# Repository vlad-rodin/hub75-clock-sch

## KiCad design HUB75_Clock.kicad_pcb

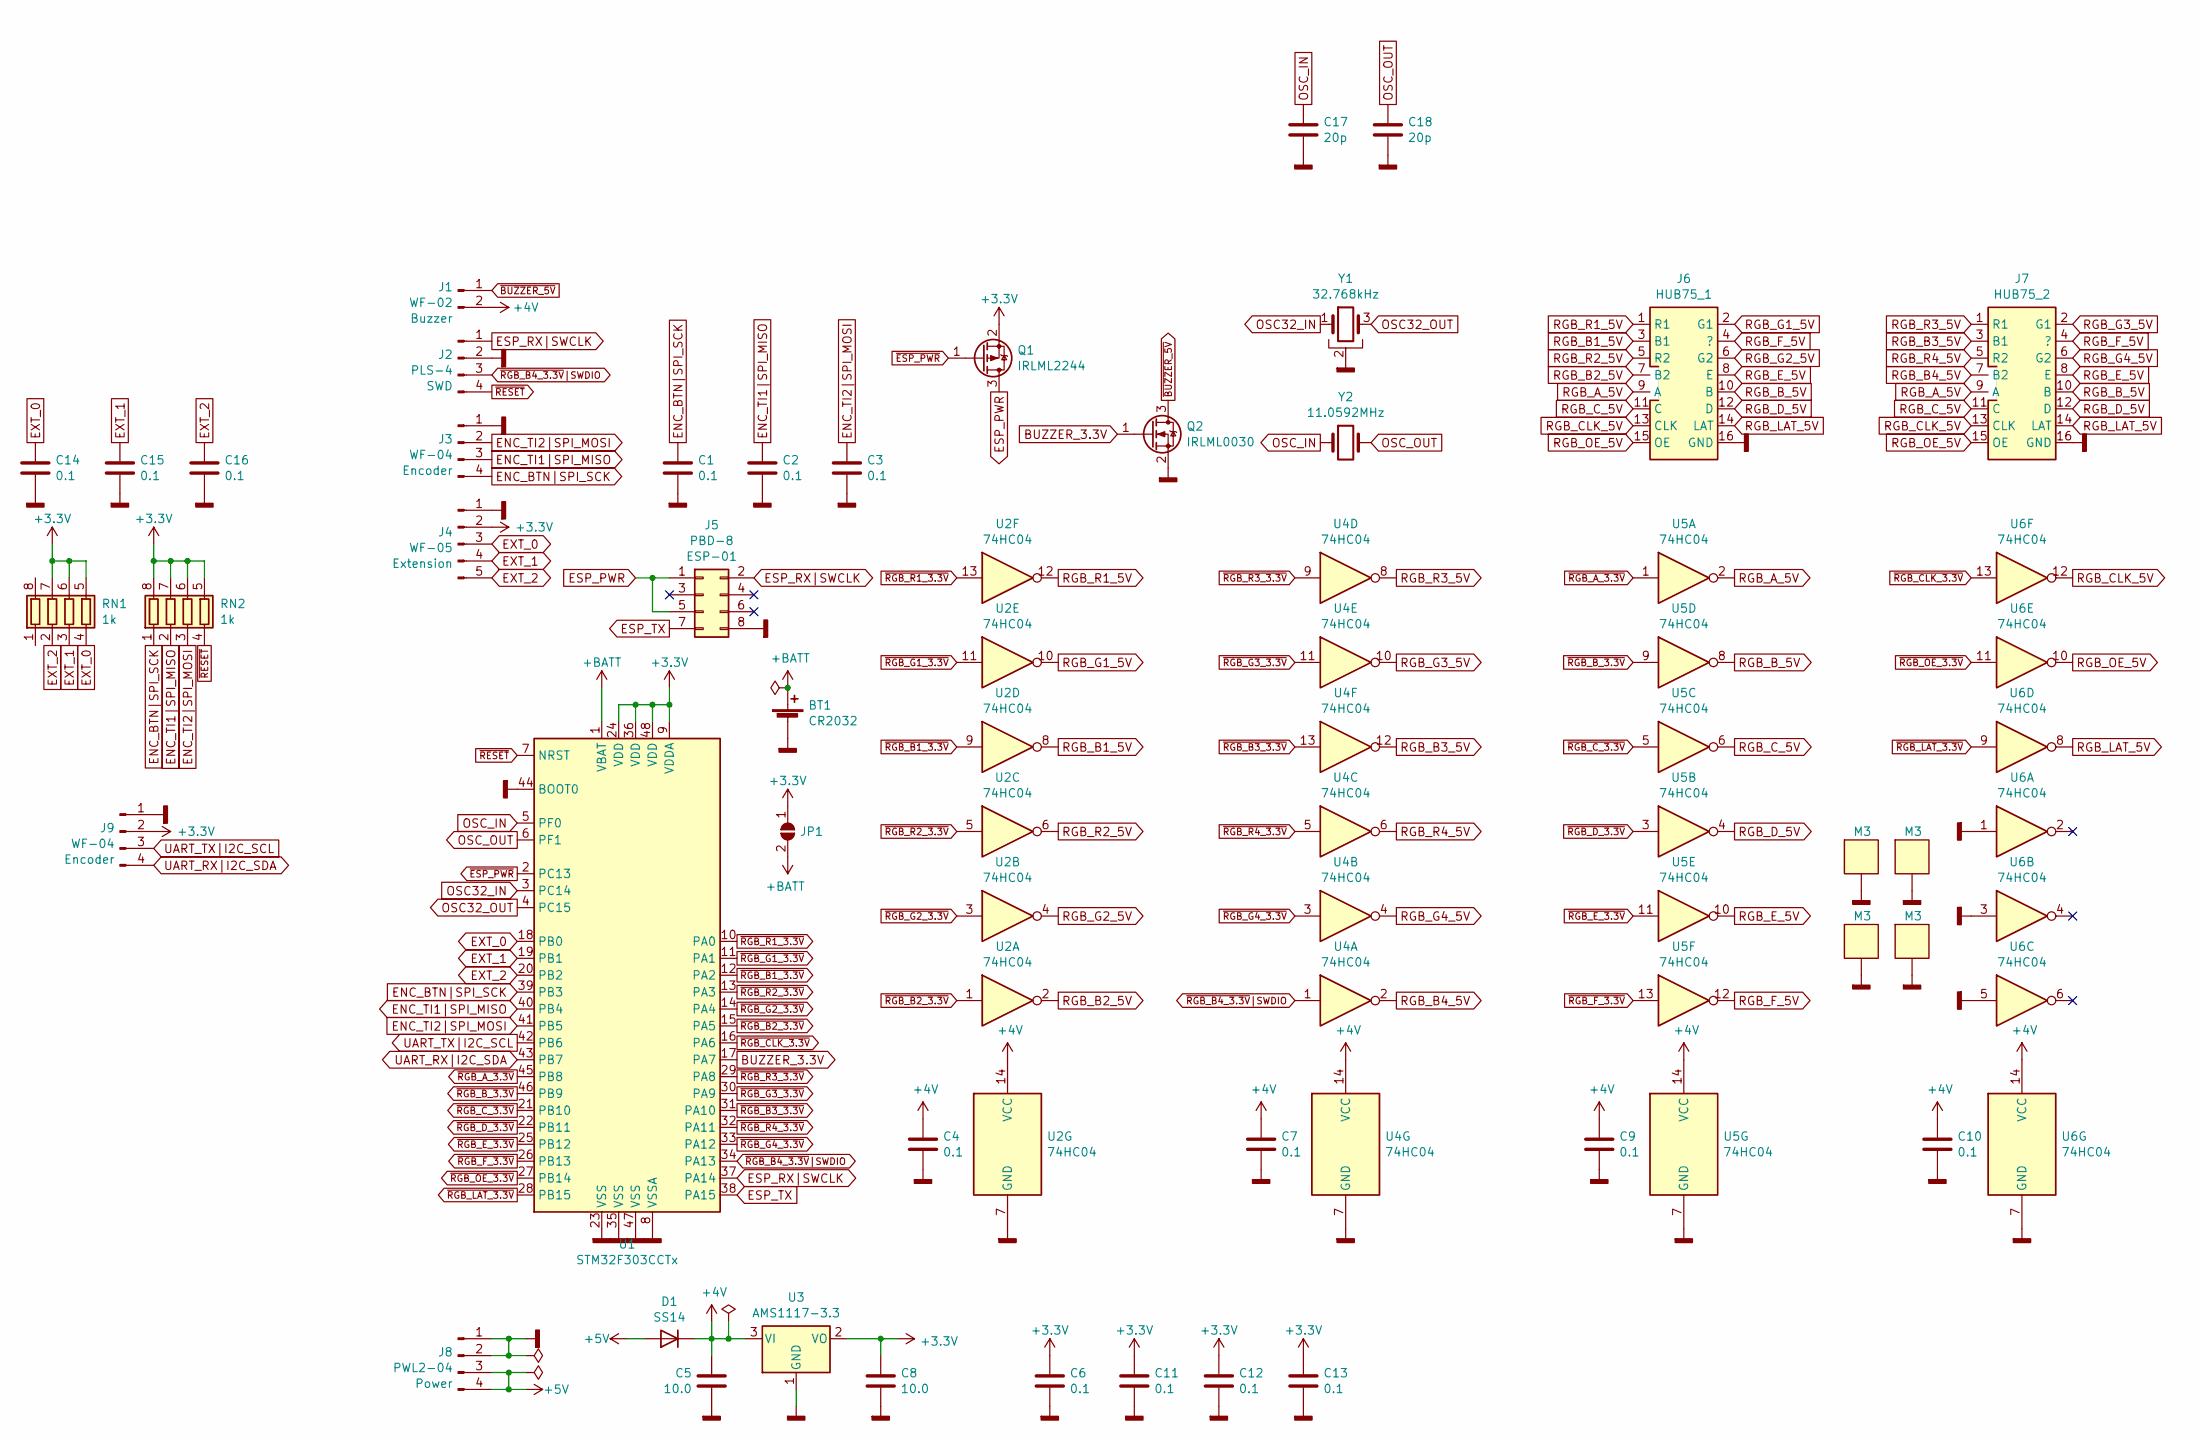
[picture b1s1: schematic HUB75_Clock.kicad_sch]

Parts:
B1, B2, B3, B4: M3; Screw_M3_9mm
BT1: CR2032
C1, C2, C3, C4, C6, C7, C9, C10, C11, C12, C13, C14, C15, C16: 0.1; C_0603
C5, C8: 10.0; C_1206
C17, C18: 20p; C_0603
D1: SS14; D_SMA
J1: WF-02
J2: PLS-4
J3, J9: WF-04
J4: WF-05
J5: PBD-8; ESP-01
J6: HUB75_1; IDC-16
J7: HUB75_2; IDC-16
J8: PWL2-04
JP1: SolderJumper_2_Open; SolderJumper-2_P1.3mm
Q1: IRLML2244; SOT-23
Q2: IRLML0030; SOT-23
RN1, RN2: 1k; R_CAT-16-4
U1: STM32F303CCTx; LQFP-48_7x7mm_P0.5mm
U2, U4, U5, U6: 74HC04; TSSOP-14_4.4x5mm_P0.65mm
U3: AMS1117-3.3; AMS1117
Y1: 32.768kHz; Crystal_Clock_SMD
Y2: 11.0592MHz; Crystal_HC-49SMD

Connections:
+3V3: C6.1, C8.1, C11.1, C12.1, C13.1, J4.2, J9.2, JP1.1 (A), Q1.2 (S), RN1.5 (R4.2), RN1.6 (R3.2), RN1.7 (R2.2), RN2.5 (R4.2), RN2.6 (R3.2), RN2.7 (R2.2), RN2.8 (R1.2), U1.9 (VDDA), U1.24 (VDD), U1.36 (VDD), U1.48 (VDD), U3.2 (VO)
+4V: C4.1, C5.1, C7.1, C9.1, C10.1, D1.1 (K), J1.2, U2.14 (VCC), U3.3 (VI), U4.14 (VCC), U5.14 (VCC), U6.14 (VCC)
+5V: D1.2 (A), J8.3, J8.4
+BATT: BT1.1 (+), JP1.2 (B), U1.1 (VBAT)
BUZZER_3.3V: Q2.1 (G), U1.17 (PA7)
ENC_BTN|SPI_SCK: C1.1, J3.4, RN2.1 (R1.1), U1.39 (PB3)
ENC_TI1|SPI_MISO: C2.1, J3.3, RN2.2 (R2.1), U1.40 (PB4)
ENC_TI2|SPI_MOSI: C3.1, J3.2, RN2.3 (R3.1), U1.41 (PB5)
ESP_PWR: J5.1, J5.5, Q1.3 (D)
ESP_RX|SWCLK: J2.1, J5.2, U1.37 (PA14)
ESP_TX: J5.7, U1.38 (PA15)
EXT_0: C14.1, J4.3, RN1.4 (R4.1), U1.18 (PB0)
EXT_1: C15.1, J4.4, RN1.3 (R3.1), U1.19 (PB1)
EXT_2: C16.1, J4.5, RN1.2 (R2.1), U1.20 (PB2)
GNDD: B1.1, B2.1, B3.1, B4.1, BT1.2 (-), C1.2, C2.2, C3.2, C4.2, C5.2, C6.2, C7.2, C8.2, C9.2, C10.2, C11.2, C12.2, C13.2, C14.2, C15.2, C16.2, C17.2, C18.2, J2.2, J3.1, J4.1, J5.8, J6.16 (GND), J7.16 (GND), J8.1, J8.2, J9.1, Q2.2 (S), U1.8 (VSSA), U1.23 (VSS), U1.35 (VSS), U1.44 (BOOT0), U1.47 (VSS), U2.7 (GND), U3.1 (GND), U4.7 (GND), U5.7 (GND), U6.1, U6.3, U6.5, U6.7 (GND), Y1.2
OSC32_IN: U1.3 (PC14), Y1.1
OSC32_OUT: U1.4 (PC15), Y1.3
OSC_IN: C17.1, U1.5 (PF0), Y2.1
OSC_OUT: C18.1, U1.6 (PF1), Y2.2
RGB_A_5V: J6.9 (A), J7.9 (A), U5.2
RGB_B1_5V: J6.3 (B1), U2.8
RGB_B2_5V: J6.7 (B2), U2.2
RGB_B3_5V: J7.3 (B1), U4.12
RGB_B4_5V: J7.7 (B2), U4.2
RGB_B_5V: J6.10 (B), J7.10 (B), U5.8
RGB_CLK_5V: J6.13 (CLK), J7.13 (CLK), U6.12
RGB_C_5V: J6.11 (C), J7.11 (C), U5.6
RGB_D_5V: J6.12 (D), J7.12 (D), U5.4
RGB_E_5V: J6.8 (E), J7.8 (E), U5.10
RGB_F_5V: J6.4 (?), J7.4 (?), U5.12
RGB_G1_5V: J6.2 (G1), U2.10
RGB_G2_5V: J6.6 (G2), U2.4
RGB_G3_5V: J7.2 (G1), U4.10
RGB_G4_5V: J7.6 (G2), U4.4
RGB_LAT_5V: J6.14 (LAT), J7.14 (LAT), U6.8
RGB_OE_5V: J6.15 (OE), J7.15 (OE), U6.10
RGB_R1_5V: J6.1 (R1), U2.12
RGB_R2_5V: J6.5 (R2), U2.6
RGB_R3_5V: J7.1 (R1), U4.8
RGB_R4_5V: J7.5 (R2), U4.6
UART_RX|I2C_SDA: J9.4, U1.43 (PB7)
UART_TX|I2C_SCL: J9.3, U1.42 (PB6)
~BUZZER_5V: J1.1, Q2.3 (D)
~ESP_PWR: Q1.1 (G), U1.2 (PC13)
~RESET: J2.4, RN2.4 (R4.1), U1.7 (NRST)
~RGB_A_3.3V: U1.45 (PB8), U5.1
~RGB_B1_3.3V: U1.12 (PA2), U2.9
~RGB_B2_3.3V: U1.15 (PA5), U2.1
~RGB_B3_3.3V: U1.31 (PA10), U4.13
~RGB_B4_3.3V|SWDIO: J2.3, U1.34 (PA13), U4.1
~RGB_B_3.3V: U1.46 (PB9), U5.9
~RGB_CLK_3.3V: U1.16 (PA6), U6.13
~RGB_C_3.3V: U1.21 (PB10), U5.5
~RGB_D_3.3V: U1.22 (PB11), U5.3
~RGB_E_3.3V: U1.25 (PB12), U5.11
~RGB_F_3.3V: U1.26 (PB13), U5.13
~RGB_G1_3.3V: U1.11 (PA1), U2.11
~RGB_G2_3.3V: U1.14 (PA4), U2.3
~RGB_G3_3.3V: U1.30 (PA9), U4.11
~RGB_G4_3.3V: U1.33 (PA12), U4.3
~RGB_LAT_3.3V: U1.28 (PB15), U6.9
~RGB_OE_3.3V: U1.27 (PB14), U6.11
~RGB_R1_3.3V: U1.10 (PA0), U2.13
~RGB_R2_3.3V: U1.13 (PA3), U2.5
~RGB_R3_3.3V: U1.29 (PA8), U4.9
~RGB_R4_3.3V: U1.32 (PA11), U4.5

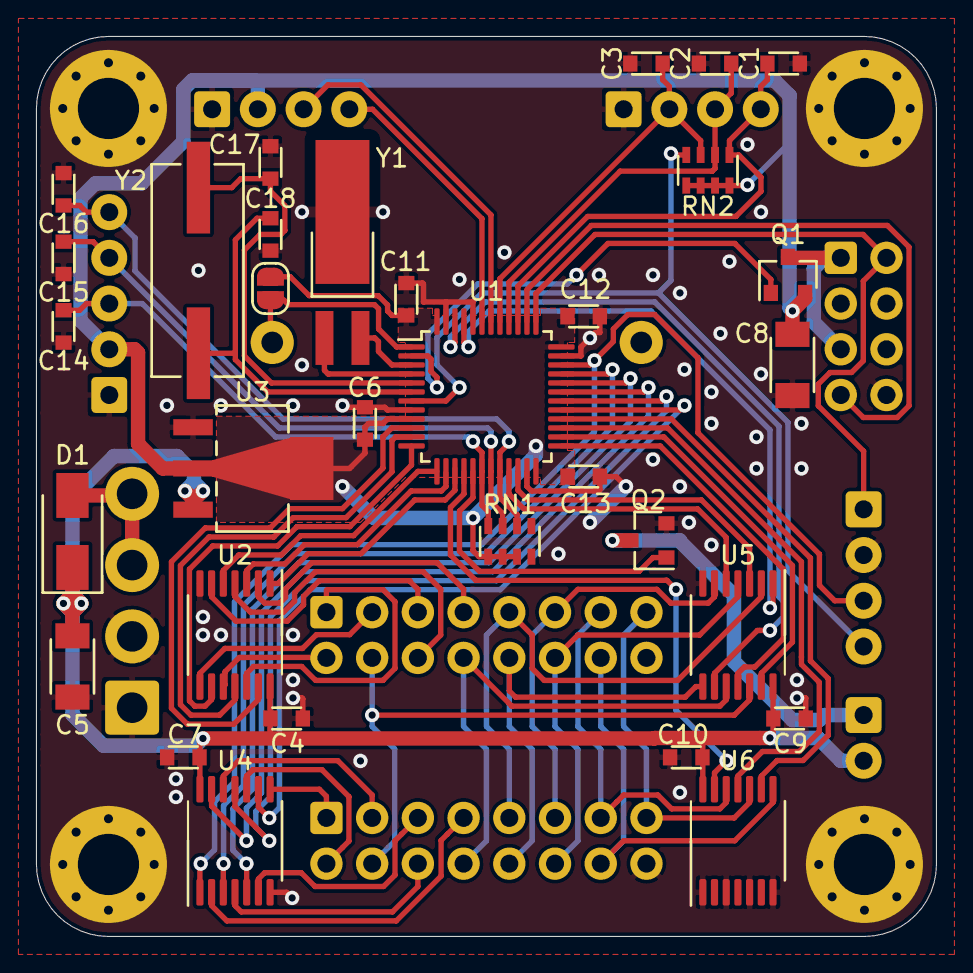
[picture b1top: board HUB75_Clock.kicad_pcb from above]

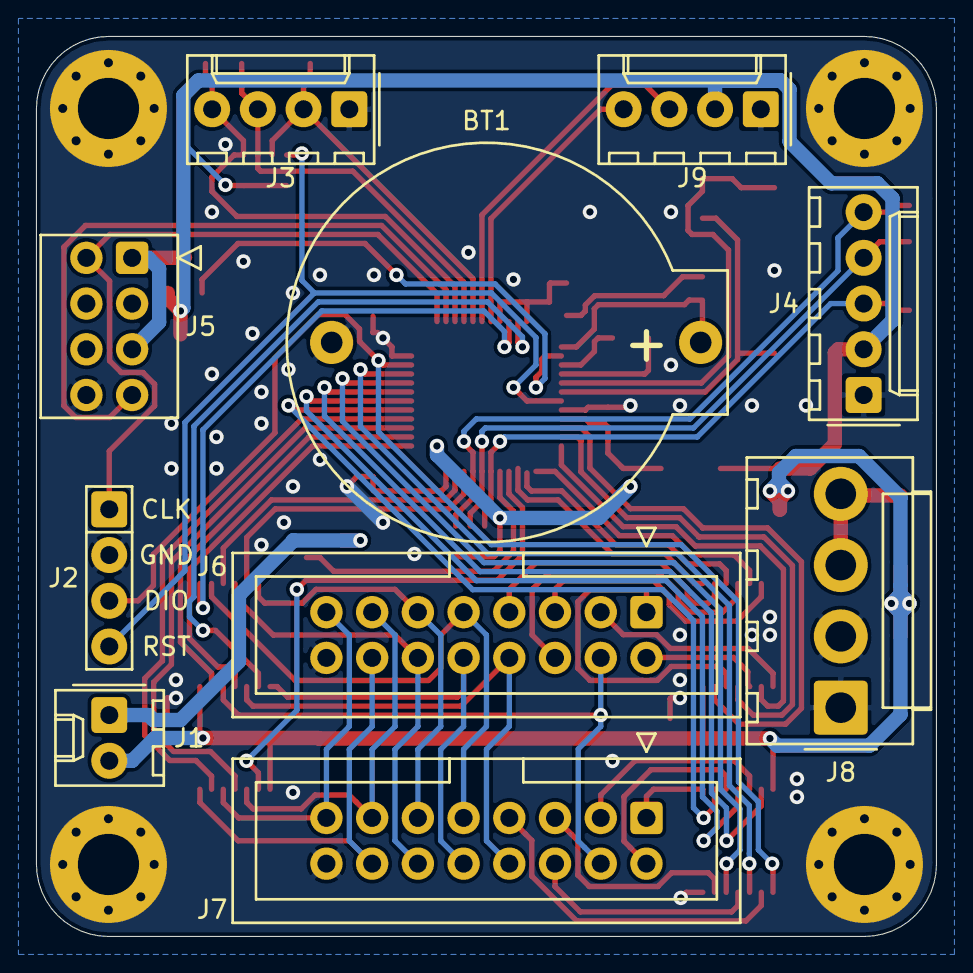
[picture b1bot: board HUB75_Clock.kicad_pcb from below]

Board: 2 copper layers, 50.0 x 50.0 mm, 46 parts (10 on the bottom side), 66 nets.

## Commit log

2023-03-19 initial
2023-03-19 updated pathes for kicad 6
2023-03-19 ignore fp-info-cache
